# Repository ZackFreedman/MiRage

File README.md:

# MiRage Modular Keyboard
## © 2021 Zack Freedman of Voidstar Lab
## Licensed Creative Commons 4.0 Attribution Noncommercial Share-Alike

The MiRage is a 60% ortholinear keyboard with three clickable OLED displays, intended for Kailh Choc switches and running custom CircuitPython firmware on a Seeedstudio Xiao RP2040. 

***THIS PROJECT IS INCOMPLETE. DO NOT MAKE IT.***

The PCB can be populated as-is for a "plank" keyboard or broken in half for a split board. The right half can be used independently as the Rage Pad numberpad/macro pad/stream deck.

This was designed for a YouTube video on my channel: https://youtu.be/Fg0V5M0llaE It will be improved and sold as a kit, and will form part of a larger project called the Fata Morgana cyberdeck.

Fusion 360 model: https://a360.co/3vEh6YI

The PCB, firmware, keymaps, and models have major issues that need to be fixed before moving forward. ***This project is not ready to be reproduced. Do not attempt to make it.*** Keymap instructions, assembly guide, BOM, and other documentation will be provided once the project is ready for release.

My component choices are final. Attempts to change my mind will be roasted in a future video.

Libraries are temporarily included for testing purposes. These will be replaced by references on release.

Keymaps are lists of bindings in the format:
R\[Row #\], K\[Key #\]: \[Key name (optional)\] # Comments start with a hash
	On press: \[Command(s) to perform once as soon as user presses key\]
	On click: \[Command(s) to perform when user presses and releases key within a few hundred milliseconds\]
	On double-click: \[Command(s) to perform when user presses and releases key twice within a few hundred milliseconds. The dash in 'double-click' is not optional.\]
	On hold: \[Command(s) to perform when user holds key for more than a few hundred ms. These generally repeat or remain in effect until the key is released.\]
	On release: \[Command(s) to perform once when user releases key. This is done after On Click and On Double-Click events are finished, and after ongoing On Hold events are cleaned up.\]

Actions you can bind to a key or event:
- `LEFT SHIFT`: Specify key bindings by naming them in all caps. You can see all the available key names in `keynames.py`. Key names must be in all caps. Spaces are optional. If a key is bound inline, it binds all events.
- `Click LEFT SHIFT`: This key will be pressed and instantly released a single time, even if this is called by an On Hold event. Clicking a key that's already Pressed will release, press, and release it.
- `Press LEFT SHIFT`: This key will be pressed indefinitely. Pressing a key that's already Pressed has no effect. Remember to add a way to release it...
- `Release LEFT SHIFT`: This key will be released. No effect if the key is not Pressed.
- `CTRL + ALT + DELETE`: Performs an operation on multiple keys simultaneously. You can Click, Press, Release, or straight-up bind key combos as if they were individual keys! Spaces around the plus signs are optional.
- `Switch to Numpad Layer`: Invokes specified layer indefinitely. This is case-insensitive. You don't need to include the layer's extension. Make sure to read the Layer Gotchas below!
- `Leave Numpad Layer`: If specified layer is currently invoked, dismisses it.
- `Switch to Numpad Layer until released`: Invokes the specified layer as long as this key remains held, and dismisses it when released. Cannot be bound to On Press, On Click, On Double-Click, or On Release events. **While in effect, layers above the one that defined this action do not apply to this key**.
- `Toggle Numpad Layer`: Acts as a Switch To action if specified layer is not currently in effect, and a Leave action if it is. Note that this can be blocked by layers above it, so make sure the new layer leaves this key open!
- `Go home`: Dismisses all invoked layers.
- `Type "Hello world!"`: Types the specified string a single time, one letter at a time. **Don't put double quotes and commas in the string!** Use `[DOUBLE QUOTES]` and `[COMMA]` instead! Any necessary keys that are currently Pressed will be released, pressed, and released again.
- `Type "Hello World!" repeatedly`: When bound to an On Press or On Hold event, types the string over and over. Extremely annoying.
- `wait 200ms`: Blocks everything for that much time. You can specify milliseconds, seconds, or minutes, in full or using ms, msec, sec, s, m, or min. Used in command sequences.
- `Click WIN+R, wait 200ms, type "cmd", click ENTER`: Sequence any combination of actions with commas. Each action is performed in its entirety before moving on. The On Hold behavior of a command sequence is not yet defined.
- `Nothing`: Allows keys on upper layers to block actions on lower layers without any side effects.
- `Pass through`: Sends this operation to the next lowest layer.
- `Reload keymaps`: Triggers a Go Home action, then reloads all the keymaps. 
- `Reset keyboard`: Triggers a software reset - disconnects from PC, reloads keymaps, and reconnects.
- `Bootloader`: Enters UF2 bootloader - disconnects from PC, kills CircuitPython, and reconnects as UF2 flash drive. **There is no way to return from the bootloader to the code without unplugging the keyboard.** This is an inbuilt limit of the bootloader and beyond my control.

Row and key numbers are zero-indexed, and refer to the physical placement of the keys on the keyboard. **These have nothing to do with the schematic. It's common sense numbering** Row 0, Key 0 is the top-left key.

Whitespace and line terminators are irrelevant. You can even use tabs, you sick bastard. UTF-8 encoding is strongly recommended; not sure how well Python handles bigger characters.

You can actually define the same key and same key action multiple times in the same map. This has the same effect as creating Sequences, and is extremely obnoxious to debug. I can't prevent you from doing it, but I can say "I told you so."

Layer Gotchas!
- Each layer's name is the same as the filename of the keymap that defined it, and is case- and extension-insensitive. **If multiple keymap files have the same name with different capitalization, the keyboard will crash on purpose just to spite you.**
- One layer must be called Base Layer. This is not optional. **The keyboard will not boot unless there's an applicable Base Layer.**
- The Base Layer is always in effect. When another layer is invoked, it's "stacked" on top. Invoking another layer stacks it on the other layer, and so on.
- When a key event happens, it's sent to the topmost layer. If that layer doesn't handle it, the next layer is checked, and so on. If you want the event to fall through anyways, such as in a sequence, use the `Pass through` action.
- Layer-related actions **DO NOT** apply immediately. Instead, the system reads every key, completes every Action fired, then applies any layer actions. This makes the layer switching process more predictable if multiple keys were pressed. 
- When a layer is invoked, if it's already in the stack, it's moved to the top.
- You cannot invoke or dismiss the Base Layer. Attempting to do so has no effect.
- The layer(s) selected by Layer Select Widgets have special slots above the Base Layer and just below the layer stack. If multiple clicky displays have Layer Select Widgets, the top screen layer is just below the layer stack and the bottom screen layer just above the Base Layer.
- If a layer selected by a Layer Select Widget is invoked, it moves from its special slot to the top of the stack. If it's dismissed, it returns to its special slot.
- Folders are provided for MiRage and Rage keymaps. Only the relevant ones apply.
- *Needs to be implemented:* When a layer is dismissed, if one or more keys with On Hold events defined by that layer are held, the On Hold ends. If one or more held keys have an On Release event, it's called. Pass Through actions in these events are ignored.

PCB problems to fix:
- VDD and VSS supply pins of PCA9505 I/O expanders are reversed
- RESET pins of PCA9505s must be pulled up
- Choc footprints will be extended to support Cherry MX switches
- Cut relief under microcontroller footprint for Adafruit QT PY. This part is **NOT** currently compatible.
- Increase size and number of breakaway tabs
- Right-angle headers are too far apart
- Add at least 4 keys
- Bottom screws are blocked by lowest row of keycaps
- Split is shifted one row to the left from usual typing position

Enclosure problems to fix: 
- Missing holes to access BOOT and RESET buttons
- Missing holes to view onboard LEDs
- Cutout for USB cable is too small 
- Rubber foot relief diameter too small and prone to sagging
- Bottom feet are too far from edges
- A small amount of PCB text is visible - poor fit and finish
- Magnetic applique falls off too easily
- Plank enclosure has header relief on wrong side
- Display buttons can crack if mashed down very hard

Code problems to fix (that I can remember off the top of my head, there are a lot)
- Rage board not implemented (not detected or automatically switched)
- Unplugging left side during runtime causes crash
- Code needs to be sped up about 200%
- Widget updating code needs to be sped up about 5000%
- Rage keymaps are missing layer switches
- Only key bindings can be defined inline
- Interactions between key event bindings and inline key bindings are unspecified
- Hold events lag, as if a click or double-click event were also bound
- Double-clicking also fires Click event
- Ongoing Hold events end sloppily if a layer switch overrides that binding
- No visual feedback for syntax errors, exceptions, layer switches, modal Lock keys, etc
- We need more widgets
- Fallback behavior in case of keymap errors
- Occasional failure to auto-run code on boot
- Including a comma in a 'Type' command crashes parser 
- If a key down command is sent then a Bootloader command runs, the key is never released
- Configuration setting is needed to redefine WINDOWS and ALT to GUI and OPTION 
- **Poor performance is due to CircuitPython, not I/O expanders. These I/O expanders can be polled over 1,000 times a second. This code would be MASSIVELY slower if a matrix were used instead of I/O expanders.**

Additional things to create:
- Plank enclosure without 3.5mm plug relief
- Split enclosure with header relief
- Rage (right hand) enclosure without 3.5mm plug relief
- Dashboard widget
- Widget that interacts with desktop
- Set typing speed 
- Enable/disable NKRO (hardcoded enabled for now due to nature of boot.py)
- Config file with widget assignments, click/hold timeout, base repeat rate, etc
- ZIF connectors to attach the MiRage to other Fata Morgana components via ribbon cables

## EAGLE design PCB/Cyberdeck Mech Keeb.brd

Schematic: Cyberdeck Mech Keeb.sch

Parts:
C1, C2, C3, C4, C5, C6, C19: 0.1uF; C0603K
C7, C8, C9, C13, C16: 1uF; C0603K
C10, C11, C12, C14, C15: 4.7uF; C0603K
C17, C18: 4.7uF; C0805
CN1, CN2, CN3, CN4: SATA
D1, D2, D3: NVRB0530; SOD-123FL
DISPLAY2: EINK-2.7
IC1, IC2, IC3, IC4, IC5: PCA9555D; SO24
IC6, IC7: 74HC30D; SO14
JP1, JP2, JP5, JP6: HEADER-0.1"-2.54MM-7POS; 2.54MM-7POS-SMD-RIGHTANGLE
L1: 10uH; CDRH6D12
MOD1: MOUDLE-SEEEDUINO-XIAO; MOUDLE14P-2.54-21X17.8MM
Q1: SI1308EDL; SOT323
R1, R2: 4.7k; R0603
R3, R4, R5, R6, R7, R8, R9, R10, R12, R13, R14: 10k; R0603
R11: 0.47; R0603
SJ1, SJ2: SOLDERJUMPER_2WAYT; SJ_2
SW1, SW2, SW5, SW6, SW7, SW8, SW9, SW10, SW11, SW12, SW13, SW14, SW15, SW16, SW17, SW18, SW19, SW20, SW21, SW22, SW23, SW24, SW25, SW26, SW27, SW28, SW29, SW30, SW31, SW32, SW33, SW34, SW35, SW36, SW37, SW38, SW39, SW40, SW41, SW42, SW43, SW44, SW45, SW46, SW47, SW48, SW49, SW50, SW51, SW52, SW53, SW54, SW55, SW56, SW57, SW58, SW59, SW60, SW61, SW62, SW63, SW64, SW65, SW66, SW67, SW68, SW69_NICE, SW70, SW72, SW73: KEYSWITCH-MIRAGE-KITCHEN-SINK; CHOC-AND-MX-SOCKET-LED-MIRAGE-KITCHEN-SINK
X3: 52745-2490
X4: 52745-0690

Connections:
+3V3: C4.1, C5.1, C6.1, C7.2, C18.1, CN3.P$7, CN4.P$7, IC3.3 (A2), IC3.21 (A0), IC3.24 (VDD), IC5.3 (A2), IC5.24 (VDD), IC6.14 (VCC), JP5.1, JP6.7, L1.P$1 (1), MOD1.12 (3V3), R1.2, R2.2, R3.2, R10.2, R12.2, R13.2, X3.9, X3.10, X3.17, X4.3
+5V: CN3.P$6, CN4.P$6, JP5.2, JP6.6, MOD1.14 (5V), SW1.+1 (VDD), SW2.+1 (VDD), SW13.+1 (VDD), SW14.+1 (VDD), SW15.+1 (VDD), SW16.+1 (VDD), SW17.+1 (VDD), SW18.+1 (VDD), SW25.+1 (VDD), SW26.+1 (VDD), SW27.+1 (VDD), SW28.+1 (VDD), SW29.+1 (VDD), SW30.+1 (VDD), SW37.+1 (VDD), SW38.+1 (VDD), SW39.+1 (VDD), SW40.+1 (VDD), SW41.+1 (VDD), SW42.+1 (VDD), SW49.+1 (VDD), SW50.+1 (VDD), SW51.+1 (VDD), SW52.+1 (VDD), SW53.+1 (VDD), SW54.+1 (VDD), SW58.+1 (VDD), SW59.+1 (VDD), SW60.+1 (VDD), SW61.+1 (VDD), SW62.+1 (VDD)
+5V/2: CN1.P$6, CN2.P$6, JP1.2, JP2.6, SW5.+1 (VDD), SW6.+1 (VDD), SW7.+1 (VDD), SW8.+1 (VDD), SW9.+1 (VDD), SW10.+1 (VDD), SW11.+1 (VDD), SW12.+1 (VDD), SW19.+1 (VDD), SW20.+1 (VDD), SW21.+1 (VDD), SW22.+1 (VDD), SW23.+1 (VDD), SW24.+1 (VDD), SW31.+1 (VDD), SW32.+1 (VDD), SW33.+1 (VDD), SW34.+1 (VDD), SW35.+1 (VDD), SW36.+1 (VDD), SW43.+1 (VDD), SW44.+1 (VDD), SW45.+1 (VDD), SW46.+1 (VDD), SW47.+1 (VDD), SW48.+1 (VDD), SW55.+1 (VDD), SW56.+1 (VDD), SW57.+1 (VDD), SW63.+1 (VDD), SW64.+1 (VDD), SW65.+1 (VDD), SW66.+1 (VDD), SW67.+1 (VDD), SW68.+1 (VDD), SW69_NICE.+1 (VDD), SW70.+1 (VDD), SW72.+1 (VDD), SW73.+1 (VDD)
COL1LED: SW72.DI1 (DI), SW73.DO1 (DO)
COL2LED: SW7.DO1 (DO), SW65.DI1 (DI)
COL3LED: SW5.DI1 (DI), SW55.DO1 (DO)
COL4LED: SW8.DI1 (DI), SW9.DO1 (DO)
COL5LED: SW46.DO1 (DO), SW56.DI1 (DI)
COL6LED: SW10.DI1 (DI), SW11.DO1 (DO)
COL7LED: SW57.DI1 (DI), SW63.DO1 (DO)
COL8LED: SW13.DI1 (DI), SW14.DO1 (DO)
COL9LED: SW50.DI1 (DI), SW58.DO1 (DO)
COL10LED: SW15.DI1 (DI), SW16.DO1 (DO)
COL11LED: SW59.DI1 (DI), SW60.DO1 (DO)
COL12LED: SW17.DI1 (DI), SW18.DO1 (DO)
COL13LED: SW2.DO1 (DO), SW62.DI1 (DI)
D0: MOD1.1 (PA02_A0_D0)
D1: MOD1.2 (PA4_A1_D1)
D6: MOD1.7 (PB08_A6_D6_TX)
DISPLAY_BUSY: MOD1.10 (PA5_A9_D9_MISO), X3.16
DISPLAY_RESET: IC3.20 (I/O1.7), R13.1, X3.15, X4.4
EXPANDER0_INT: IC4.1 (!INT), IC7.4 (I3), R7.1
EXPANDER1_INT: IC2.1 (!INT), IC7.5 (I4), R6.1
EXPANDER2_INT: IC1.1 (!INT), IC7.6 (I5), R5.1
EXPANDER3_INT: IC5.1 (!INT), IC6.6 (I5), R10.1
EXPANDER4_INT: IC3.1 (!INT), IC6.1 (I0), R3.1
GDR: Q1.1 (G), R9.2, X3.23
GND: C4.2, C5.2, C6.2, C7.1, C8.1, C9.1, C10.1, C11.1, C12.1, C13.1, C14.1, C15.1, C16.1, C18.2, CN3.LEFT_TAB (TABS), CN3.P$5, CN3.RIGHT_TAB (TABS), CN4.LEFT_TAB (TABS), CN4.P$5, CN4.RIGHT_TAB (TABS), D2.C, IC3.2 (A1), IC3.12 (VSS), IC5.2 (A1), IC5.12 (VSS), IC5.21 (A0), IC6.7 (GND), JP5.3, JP6.5, MOD1.13 (GND), R4.1, R9.1, R11.1, SW1.CHOC1 (P1), SW1.GND1 (GND), SW1.MX1 (P1), SW2.CHOC2 (P0), SW2.GND1 (GND), SW2.MX2 (P0), SW13.CHOC1 (P1), SW13.GND1 (GND), SW13.MX1 (P1), SW14.CHOC1 (P1), SW14.GND1 (GND), SW14.MX1 (P1), SW15.CHOC1 (P1), SW15.GND1 (GND), SW15.MX1 (P1), SW16.CHOC2 (P0), SW16.GND1 (GND), SW16.MX2 (P0), SW17.CHOC1 (P1), SW17.GND1 (GND), SW17.MX1 (P1), SW18.CHOC1 (P1), SW18.GND1 (GND), SW18.MX1 (P1), SW25.CHOC1 (P1), SW25.GND1 (GND), SW25.MX1 (P1), SW26.CHOC1 (P1), SW26.GND1 (GND), SW26.MX1 (P1), SW27.CHOC1 (P1), SW27.GND1 (GND), SW27.MX1 (P1), SW28.CHOC1 (P1), SW28.GND1 (GND), SW28.MX1 (P1), SW29.CHOC1 (P1), SW29.GND1 (GND), SW29.MX1 (P1), SW30.CHOC1 (P1), SW30.GND1 (GND), SW30.MX1 (P1), SW37.CHOC1 (P1), SW37.GND1 (GND), SW37.MX1 (P1), SW38.CHOC1 (P1), SW38.GND1 (GND), SW38.MX1 (P1), SW39.CHOC1 (P1), SW39.GND1 (GND), SW39.MX1 (P1), SW40.CHOC1 (P1), SW40.GND1 (GND), SW40.MX1 (P1), SW41.CHOC1 (P1), SW41.GND1 (GND), SW41.MX1 (P1), SW42.CHOC1 (P1), SW42.GND1 (GND), SW42.MX1 (P1), SW49.CHOC1 (P1), SW49.GND1 (GND), SW49.MX1 (P1), SW50.CHOC1 (P1), SW50.GND1 (GND), SW50.MX1 (P1), SW51.CHOC1 (P1), SW51.GND1 (GND), SW51.MX1 (P1), SW52.CHOC1 (P1), SW52.GND1 (GND), SW52.MX1 (P1), SW53.CHOC1 (P1), SW53.GND1 (GND), SW53.MX1 (P1), SW54.CHOC1 (P1), SW54.GND1 (GND), SW54.MX1 (P1), SW58.CHOC2 (P0), SW58.GND1 (GND), SW58.MX2 (P0), SW59.CHOC1 (P1), SW59.GND1 (GND), SW59.MX1 (P1), SW60.CHOC1 (P1), SW60.GND1 (GND), SW60.MX1 (P1), SW61.CHOC1 (P1), SW61.GND1 (GND), SW61.MX1 (P1), SW62.CHOC1 (P1), SW62.GND1 (GND), SW62.MX1 (P1), X3.8, X3.13, X3.14, X4.6
GND2: C1.2, C2.2, C3.2, C19.2, CN1.LEFT_TAB (TABS), CN1.P$5, CN1.RIGHT_TAB (TABS), CN2.LEFT_TAB (TABS), CN2.P$5, CN2.RIGHT_TAB (TABS), IC1.3 (A2), IC1.12 (VSS), IC2.12 (VSS), IC4.2 (A1), IC4.3 (A2), IC4.12 (VSS), IC7.7 (GND), JP1.3, JP2.5, R14.1, SJ1.1, SW5.CHOC2 (P0), SW5.GND1 (GND), SW5.MX2 (P0), SW6.CHOC2 (P0), SW6.GND1 (GND), SW6.MX2 (P0), SW7.CHOC2 (P0), SW7.GND1 (GND), SW7.MX2 (P0), SW8.CHOC2 (P0), SW8.GND1 (GND), SW8.MX2 (P0), SW9.CHOC2 (P0), SW9.GND1 (GND), SW9.MX2 (P0), SW10.CHOC2 (P0), SW10.GND1 (GND), SW10.MX2 (P0), SW11.CHOC2 (P0), SW11.GND1 (GND), SW11.MX2 (P0), SW12.CHOC2 (P0), SW12.GND1 (GND), SW12.MX2 (P0), SW19.CHOC2 (P0), SW19.GND1 (GND), SW19.MX2 (P0), SW20.CHOC2 (P0), SW20.GND1 (GND), SW20.MX2 (P0), SW21.CHOC2 (P0), SW21.GND1 (GND), SW21.MX2 (P0), SW22.CHOC2 (P0), SW22.GND1 (GND), SW22.MX2 (P0), SW23.CHOC2 (P0), SW23.GND1 (GND), SW23.MX2 (P0), SW24.CHOC2 (P0), SW24.GND1 (GND), SW24.MX2 (P0), SW31.CHOC2 (P0), SW31.GND1 (GND), SW31.MX2 (P0), SW32.CHOC2 (P0), SW32.GND1 (GND), SW32.MX2 (P0), SW33.CHOC2 (P0), SW33.GND1 (GND), SW33.MX2 (P0), SW34.CHOC2 (P0), SW34.GND1 (GND), SW34.MX2 (P0), SW35.CHOC2 (P0), SW35.GND1 (GND), SW35.MX2 (P0), SW36.CHOC2 (P0), SW36.GND1 (GND), SW36.MX2 (P0), SW43.CHOC2 (P0), SW43.GND1 (GND), SW43.MX2 (P0), SW44.CHOC2 (P0), SW44.GND1 (GND), SW44.MX2 (P0), SW45.CHOC2 (P0), SW45.GND1 (GND), SW45.MX2 (P0), SW46.CHOC2 (P0), SW46.GND1 (GND), SW46.MX2 (P0), SW47.CHOC2 (P0), SW47.GND1 (GND), SW47.MX2 (P0), SW48.CHOC2 (P0), SW48.GND1 (GND), SW48.MX2 (P0), SW55.CHOC2 (P0), SW55.GND1 (GND), SW55.MX2 (P0), SW56.CHOC1 (P1), SW56.GND1 (GND), SW56.MX1 (P1), SW57.CHOC1 (P1), SW57.GND1 (GND), SW57.MX1 (P1), SW63.CHOC2 (P0), SW63.GND1 (GND), SW63.MX2 (P0), SW64.CHOC1 (P1), SW64.GND1 (GND), SW64.MX1 (P1), SW65.CHOC2 (P0), SW65.GND1 (GND), SW65.MX2 (P0), SW66.CHOC1 (P1), SW66.GND1 (GND), SW66.MX1 (P1), SW67.CHOC2 (P0), SW67.GND1 (GND), SW67.MX2 (P0), SW68.CHOC1 (P1), SW68.GND1 (GND), SW68.MX1 (P1), SW69_NICE.CHOC1 (P1), SW69_NICE.GND1 (GND), SW69_NICE.MX1 (P1), SW70.CHOC1 (P1), SW70.GND1 (GND), SW70.MX1 (P1), SW72.CHOC1 (P1), SW72.GND1 (GND), SW72.MX1 (P1), SW73.CHOC1 (P1), SW73.GND1 (GND), SW73.MX1 (P1)
INTERRUPT: IC6.8 (O), MOD1.4 (PA11_A3_D3), R4.2
LEFTER_HAND_INT: CN1.P$4, IC7.3 (I2), JP1.4
LEFTER_HAND_LED: CN1.P$3, JP1.5, SW66.DO1 (DO)
LEFT_HAND_INT: CN3.P$4, IC6.2 (I1), JP5.4
LEFT_HAND_INT': CN2.P$4, IC7.8 (O), JP2.4, R14.2
LEFT_HAND_LED: CN3.P$3, JP5.5, SW61.DO1 (DO)
LEFT_HAND_LED': CN2.P$3, JP2.3, SW12.DI1 (DI)
unnamed: SW12.DO1 (DO), SW24.DI1 (DI)
unnamed: SW24.DO1 (DO), SW36.DI1 (DI)
unnamed: SW36.DO1 (DO), SW48.DI1 (DI)
unnamed: SW48.DO1 (DO), SW63.DI1 (DI)
unnamed: SW47.DI1 (DI), SW57.DO1 (DO)
unnamed: SW13.DO1 (DO), SW25.DI1 (DI)
unnamed: SW25.DO1 (DO), SW37.DI1 (DI)
unnamed: C17.1, D2.A, D3.C
unnamed: SW35.DI1 (DI), SW47.DO1 (DO)
unnamed: SW37.DO1 (DO), SW49.DI1 (DI)
unnamed: SW23.DI1 (DI), SW35.DO1 (DO)
unnamed: SW42.DI1 (DI), SW54.DO1 (DO)
unnamed: SW54.DI1 (DI), SW62.DO1 (DO)
unnamed: C17.2, D1.A, L1.P$3 (2), Q1.3 (D)
unnamed: SW11.DI1 (DI), SW23.DO1 (DO)
unnamed: SW30.DI1 (DI), SW42.DO1 (DO)
unnamed: SW18.DI1 (DI), SW30.DO1 (DO)
unnamed: SW14.DI1 (DI), SW26.DO1 (DO)
unnamed: SW16.DI1 (DI), SW28.DO1 (DO)
unnamed: SW28.DI1 (DI), SW40.DO1 (DO)
unnamed: SW10.DO1 (DO), SW22.DI1 (DI)
unnamed: SW22.DO1 (DO), SW34.DI1 (DI)
unnamed: SW40.DI1 (DI), SW52.DO1 (DO)
unnamed: SW34.DO1 (DO), SW46.DI1 (DI)
unnamed: SW52.DI1 (DI), SW59.DO1 (DO)
unnamed: SW26.DI1 (DI), SW38.DO1 (DO)
unnamed: SW38.DI1 (DI), SW50.DO1 (DO)
unnamed: SW45.DI1 (DI), SW56.DO1 (DO)
unnamed: SW33.DI1 (DI), SW45.DO1 (DO)
unnamed: SW49.DO1 (DO), SW61.DI1 (DI)
unnamed: SW21.DI1 (DI), SW33.DO1 (DO)
unnamed: SW9.DI1 (DI), SW21.DO1 (DO)
unnamed: SW8.DO1 (DO), SW20.DI1 (DI)
unnamed: SW20.DO1 (DO), SW32.DI1 (DI)
unnamed: SW32.DO1 (DO), SW44.DI1 (DI)
unnamed: SW44.DO1 (DO), SW55.DI1 (DI)
unnamed: SW5.DO1 (DO), SW43.DI1 (DI)
unnamed: SW31.DI1 (DI), SW43.DO1 (DO)
unnamed: SW19.DI1 (DI), SW31.DO1 (DO)
unnamed: SW7.DI1 (DI), SW19.DO1 (DO)
unnamed: SW65.DO1 (DO), SW67.DI1 (DI)
unnamed: SW6.DI1 (DI), SW67.DO1 (DO)
unnamed: SW6.DO1 (DO), SW69_NICE.DI1 (DI)
unnamed: SW69_NICE.DO1 (DO), SW73.DI1 (DI)
unnamed: SW68.DI1 (DI), SW72.DO1 (DO)
unnamed: SW68.DO1 (DO), SW70.DI1 (DI)
unnamed: SW64.DI1 (DI), SW70.DO1 (DO)
unnamed: SW64.DO1 (DO), SW66.DI1 (DI)
unnamed: SW53.DO1 (DO), SW60.DI1 (DI)
unnamed: SW41.DO1 (DO), SW53.DI1 (DI)
unnamed: SW29.DO1 (DO), SW41.DI1 (DI)
unnamed: SW17.DO1 (DO), SW29.DI1 (DI)
unnamed: SW1.DO1 (DO), SW2.DI1 (DI)
unnamed: SW15.DO1 (DO), SW27.DI1 (DI)
unnamed: SW27.DO1 (DO), SW39.DI1 (DI)
unnamed: SW39.DO1 (DO), SW51.DI1 (DI)
unnamed: SW51.DO1 (DO), SW58.DI1 (DI)
PREVGH: C16.2, D1.C, X3.4
PREVGL: C12.2, D3.A, X3.2
QUAGSIRE: IC2.6 (I/O0.2)
R0C0: IC4.4 (I/O0.0), SW66.CHOC2 (P0), SW66.MX2 (P0)
R0C1: IC4.11 (I/O0.7), SW65.CHOC1 (P1), SW65.MX1 (P1)
R0C2: IC2.11 (I/O0.7), SW7.CHOC1 (P1), SW7.MX1 (P1)
R0C3: IC2.17 (I/O1.4), SW8.CHOC1 (P1), SW8.MX1 (P1)
R0C4: IC1.4 (I/O0.0), SW9.CHOC1 (P1), SW9.MX1 (P1)
R0C5: IC1.9 (I/O0.5), SW10.CHOC1 (P1), SW10.MX1 (P1)
R0C6: IC1.15 (I/O1.2), SW11.CHOC1 (P1), SW11.MX1 (P1)
R0C7: IC1.20 (I/O1.7), SW12.CHOC1 (P1), SW12.MX1 (P1)
R0C8: IC5.4 (I/O0.0), SW13.CHOC2 (P0), SW13.MX2 (P0)
R0C9: IC5.9 (I/O0.5), SW14.CHOC2 (P0), SW14.MX2 (P0)
R0C10: IC5.15 (I/O1.2), SW15.CHOC2 (P0), SW15.MX2 (P0)
R0C11: IC5.19 (I/O1.6), SW16.CHOC1 (P1), SW16.MX1 (P1)
R0C12: IC3.7 (I/O0.3), SW17.CHOC2 (P0), SW17.MX2 (P0)
R0C13: IC3.13 (I/O1.0), SW18.CHOC2 (P0), SW18.MX2 (P0)
R1C0: IC4.5 (I/O0.1), SW64.CHOC2 (P0), SW64.MX2 (P0)
R1C1: IC4.10 (I/O0.6), SW67.CHOC1 (P1), SW67.MX1 (P1)
R1C2: IC2.10 (I/O0.6), SW19.CHOC1 (P1), SW19.MX1 (P1)
R1C3: IC2.16 (I/O1.3), SW20.CHOC1 (P1), SW20.MX1 (P1)
R1C4: IC2.20 (I/O1.7), SW21.CHOC1 (P1), SW21.MX1 (P1)
R1C5: IC1.8 (I/O0.4), SW22.CHOC1 (P1), SW22.MX1 (P1)
R1C6: IC1.14 (I/O1.1), SW23.CHOC1 (P1), SW23.MX1 (P1)
R1C7: IC1.19 (I/O1.6), SW24.CHOC1 (P1), SW24.MX1 (P1)
R1C8: IC5.5 (I/O0.1), SW25.CHOC2 (P0), SW25.MX2 (P0)
R1C9: IC5.10 (I/O0.6), SW26.CHOC2 (P0), SW26.MX2 (P0)
R1C10: IC5.16 (I/O1.3), SW27.CHOC2 (P0), SW27.MX2 (P0)
R1C11: IC5.20 (I/O1.7), SW28.CHOC2 (P0), SW28.MX2 (P0)
R1C12: IC3.8 (I/O0.4), SW29.CHOC2 (P0), SW29.MX2 (P0)
R1C13: IC3.14 (I/O1.1), SW30.CHOC2 (P0), SW30.MX2 (P0)
R2C0: IC4.6 (I/O0.2), SW70.CHOC2 (P0), SW70.MX2 (P0)
R2C1: IC4.9 (I/O0.5), SW6.CHOC1 (P1), SW6.MX1 (P1)
R2C2: IC2.9 (I/O0.5), SW31.CHOC1 (P1), SW31.MX1 (P1)
R2C3: IC2.15 (I/O1.2), SW32.CHOC1 (P1), SW32.MX1 (P1)
R2C4: IC2.19 (I/O1.6), SW33.CHOC1 (P1), SW33.MX1 (P1)
R2C5: IC1.7 (I/O0.3), SW34.CHOC1 (P1), SW34.MX1 (P1)
R2C6: IC1.13 (I/O1.0), SW35.CHOC1 (P1), SW35.MX1 (P1)
R2C7: IC1.18 (I/O1.5), SW36.CHOC1 (P1), SW36.MX1 (P1)
R2C8: IC5.6 (I/O0.2), SW37.CHOC2 (P0), SW37.MX2 (P0)
R2C9: IC5.11 (I/O0.7), SW38.CHOC2 (P0), SW38.MX2 (P0)
R2C10: IC5.17 (I/O1.4), SW39.CHOC2 (P0), SW39.MX2 (P0)
R2C11: IC3.4 (I/O0.0), SW40.CHOC2 (P0), SW40.MX2 (P0)
R2C12: IC3.9 (I/O0.5), SW41.CHOC2 (P0), SW41.MX2 (P0)
R2C13: IC3.15 (I/O1.2), SW42.CHOC2 (P0), SW42.MX2 (P0)
R3C0: IC4.7 (I/O0.3), SW68.CHOC2 (P0), SW68.MX2 (P0)
R3C1: IC4.13 (I/O1.0), SW69_NICE.CHOC2 (P0), SW69_NICE.MX2 (P0)
R3C2: IC2.8 (I/O0.4), SW43.CHOC1 (P1), SW43.MX1 (P1)
R3C3: IC2.14 (I/O1.1), SW44.CHOC1 (P1), SW44.MX1 (P1)
R3C4: IC2.18 (I/O1.5), SW45.CHOC1 (P1), SW45.MX1 (P1)
R3C5: IC1.6 (I/O0.2), SW46.CHOC1 (P1), SW46.MX1 (P1)
R3C6: IC1.10 (I/O0.6), SW47.CHOC1 (P1), SW47.MX1 (P1)
R3C7: IC1.17 (I/O1.4), SW48.CHOC1 (P1), SW48.MX1 (P1)
R3C8: IC5.7 (I/O0.3), SW49.CHOC2 (P0), SW49.MX2 (P0)
R3C9: IC5.14 (I/O1.1), SW50.CHOC2 (P0), SW50.MX2 (P0)
R3C10: IC5.18 (I/O1.5), SW51.CHOC2 (P0), SW51.MX2 (P0)
R3C11: IC3.5 (I/O0.1), SW52.CHOC2 (P0), SW52.MX2 (P0)
R3C12: IC3.10 (I/O0.6), SW53.CHOC2 (P0), SW53.MX2 (P0)
R3C13: IC3.16 (I/O1.3), SW54.CHOC2 (P0), SW54.MX2 (P0)
R4C0: IC4.8 (I/O0.4), SW72.CHOC2 (P0), SW72.MX2 (P0)
R4C1: IC4.14 (I/O1.1), SW73.CHOC2 (P0), SW73.MX2 (P0)
R4C2: IC2.7 (I/O0.3), SW5.CHOC1 (P1), SW5.MX1 (P1)
R4C3: IC2.13 (I/O1.0), SW55.CHOC1 (P1), SW55.MX1 (P1)
R4C4: IC1.5 (I/O0.1), SW56.CHOC2 (P0), SW56.MX2 (P0)
R4C6: IC1.11 (I/O0.7), SW57.CHOC2 (P0), SW57.MX2 (P0)
R4C7: IC1.16 (I/O1.3), SW63.CHOC1 (P1), SW63.MX1 (P1)
R4C8: IC5.8 (I/O0.4), SW61.CHOC2 (P0), SW61.MX2 (P0)
R4C10: IC5.13 (I/O1.0), SW58.CHOC1 (P1), SW58.MX1 (P1)
R4C11: IC3.6 (I/O0.2), SW59.CHOC2 (P0), SW59.MX2 (P0)
R4C12: IC3.11 (I/O0.7), SW60.CHOC2 (P0), SW60.MX2 (P0)
R4C13: IC3.17 (I/O1.4), SW62.CHOC2 (P0), SW62.MX2 (P0)
R4C14: IC3.18 (I/O1.5), SW2.CHOC1 (P1), SW2.MX1 (P1)
R4C15: IC3.19 (I/O1.6), SW1.CHOC2 (P0), SW1.MX2 (P0)
RAGE_LEDS: MOD1.8 (PB09_A7_D7_RX), SW1.DI1 (DI)
RESE: Q1.2 (S), R11.2, X3.22
RIGHTER_HAND_INT: CN4.P$4, IC6.11 (I6), JP6.4
RIGHTER_HAND_LED: CN4.P$3, JP6.3, MOD1.3 (PA10_A2_D2)
SCK: MOD1.9 (PA7_A8_D8_SCK), X3.12
SCL: CN3.P$1, CN4.P$1, IC3.22 (SCL), IC5.22 (SCL), JP5.7, JP6.1, MOD1.6 (PA9_A5_D5_SCL), R2.1, X4.2
SCL': CN1.P$1, CN2.P$1, IC1.22 (SCL), IC2.22 (SCL), IC4.22 (SCL), JP1.7, JP2.1
SDA: CN3.P$2, CN4.P$2, IC3.23 (SDA), IC5.23 (SDA), JP5.6, JP6.2, MOD1.5 (PA8_A4_D4_SDA), R1.1, X4.1
SDA': CN1.P$2, CN2.P$2, IC1.23 (SDA), IC2.23 (SDA), IC4.23 (SDA), JP1.6, JP2.2
SDI: MOD1.11 (PA6_A10_D10_MOSI), X3.11
THIRD_HALF_SELECT: IC1.21 (A0), IC2.21 (A0), IC4.21 (A0), R8.1, SJ1.2, SJ2.2
THIS_IS_LEFTER: IC4.19 (I/O1.6), SJ2.1
THIS_IS_RIGHTER: IC4.17 (I/O1.4), SJ2.3
TOUCH_INT: IC6.12 (I7), R12.1, X4.5
TSCL: X3.19
TSDA: X3.18
VCCIO: C1.1, C2.1, C3.1, C19.1, CN1.P$7, CN2.P$7, IC1.2 (A1), IC1.24 (VDD), IC2.2 (A1), IC2.3 (A2), IC2.24 (VDD), IC4.24 (VDD), IC7.14 (VCC), JP1.1, JP2.7, R5.2, R6.2, R7.2, R8.2, SJ1.3
VCOM: C13.2, X3.1
VDD: C8.2, X3.7
VGH: C15.2, X3.20
VGL: C14.2, X3.21
VPP: C9.2, X3.6
VSH: C10.2, X3.5
VSL: C11.2, X3.3

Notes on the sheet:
Seeeduino XIAO (RP2040 if possible)
CSB

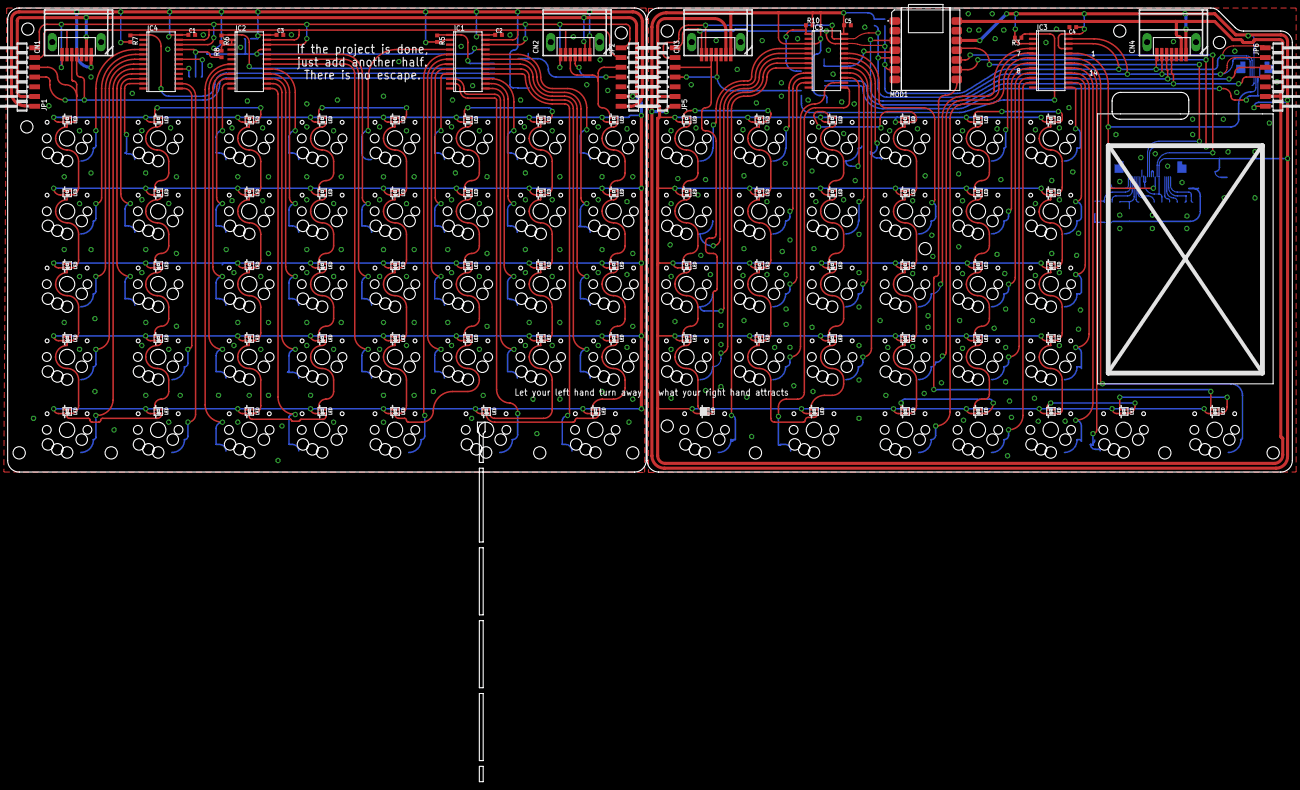
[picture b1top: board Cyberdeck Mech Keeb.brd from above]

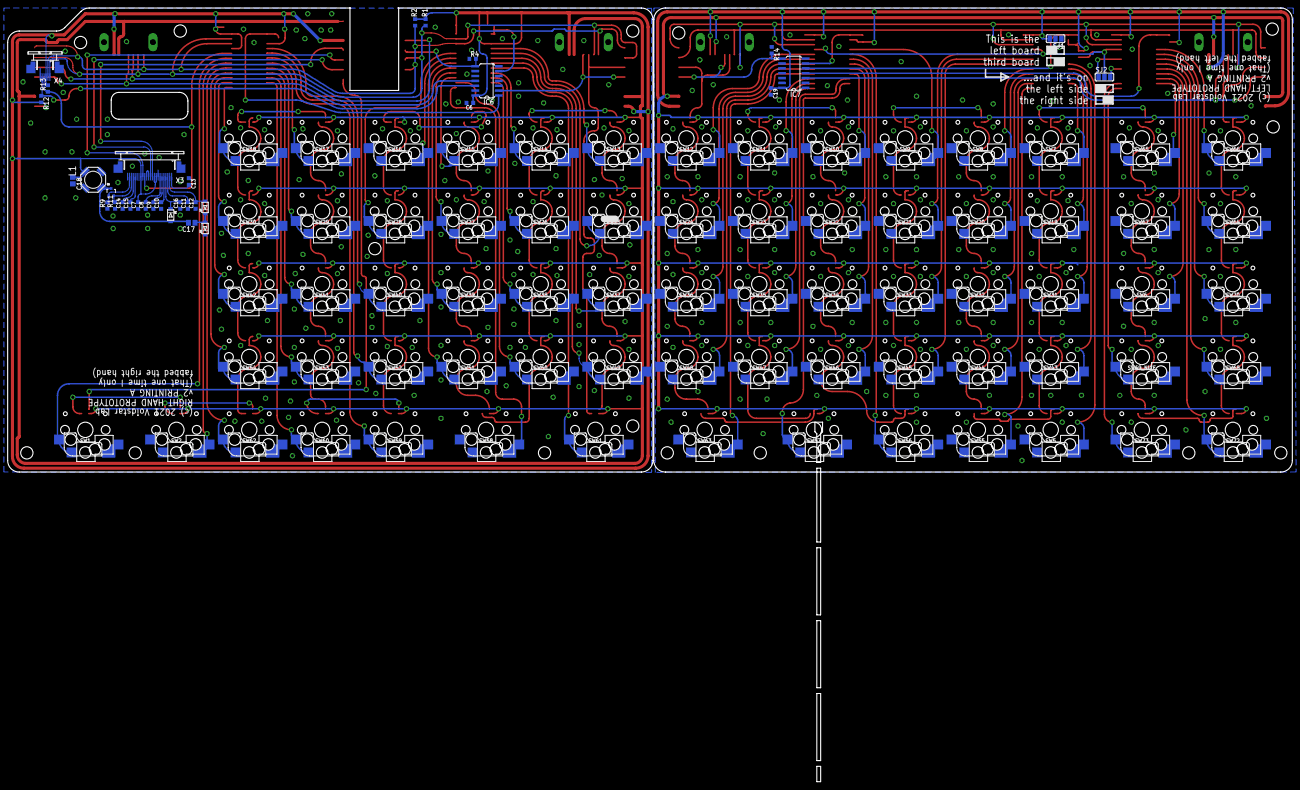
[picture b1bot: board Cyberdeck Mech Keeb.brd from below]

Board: 2 copper layers, 335.0 x 201.8 mm, 129 parts (33 on the bottom side), 184 nets.

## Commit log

2021-10-24 Initial commit
    I need a vacation
2021-10-24 Added video URL
2021-10-29 Put keymap format under ticks for better reading
2021-10-31 list declration oprimized
2021-11-09 [parser] Refactor parser to use tokenization.
    Refactors parser to process source string as token list.
    Fixes a number of small bugs, adds a couple small features, and
    adds a bunch of test cases to keep the language running
2022-06-14 Gen 2 PCB
2022-06-24 fixes small typos in README.md

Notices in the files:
PCB/Cyberdeck Mech Keeb.brd:
(c) 2021 Voidstar Lab
parts and their libraries:
SparkFun-DiscreteSemi: Licensing: CC v3.0 Share-Alike You are welcome to use this library for commercial purposes.
